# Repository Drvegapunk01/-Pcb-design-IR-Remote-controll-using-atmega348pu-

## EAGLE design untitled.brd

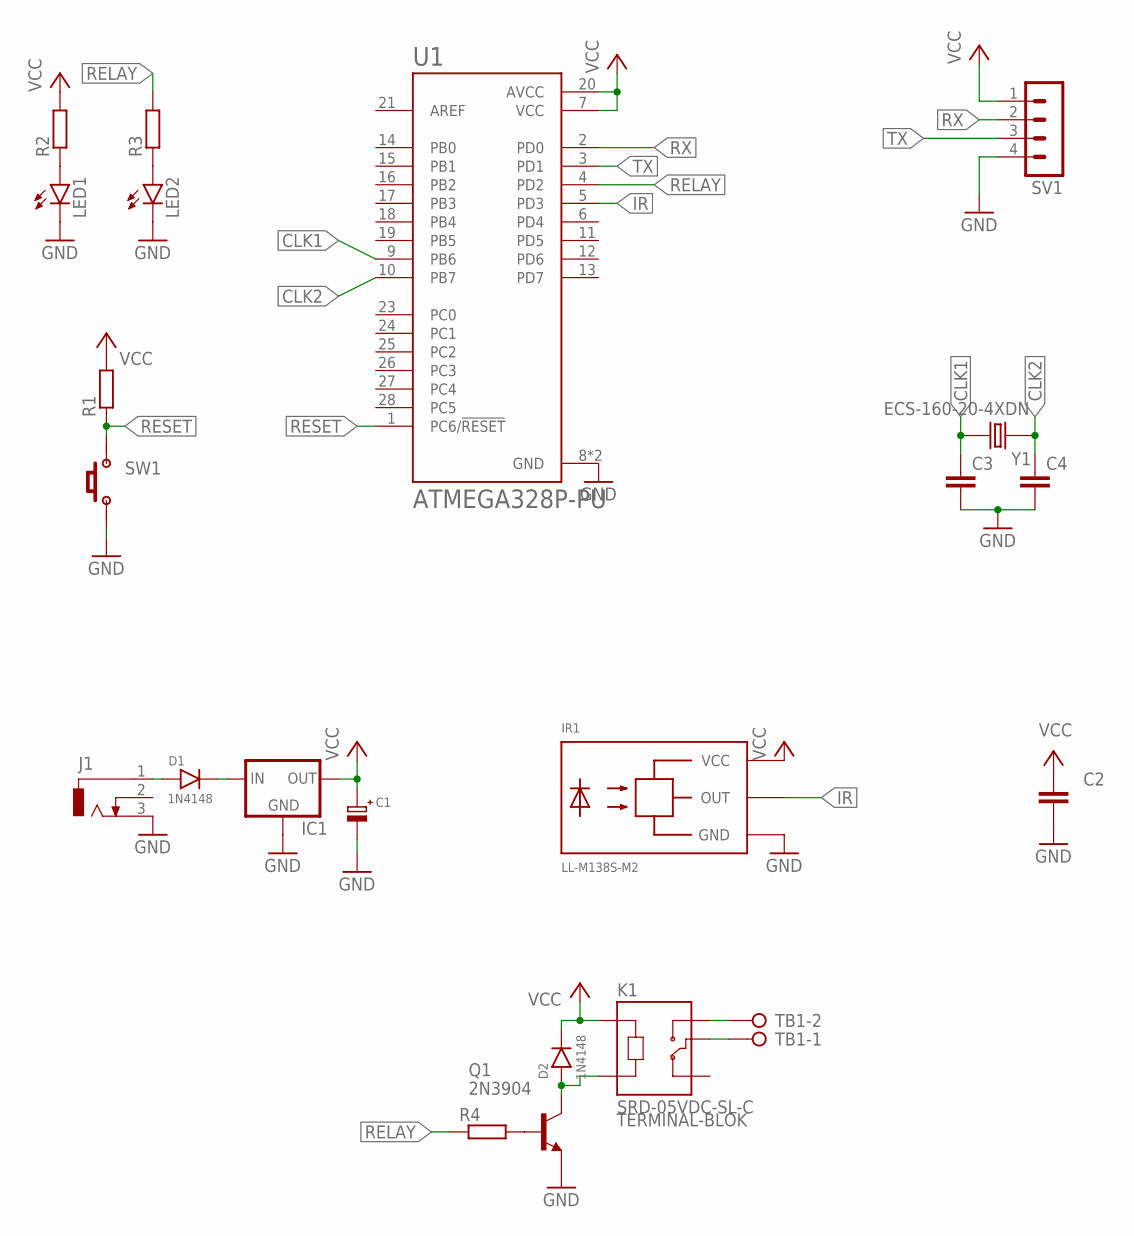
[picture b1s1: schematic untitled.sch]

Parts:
C1: CAP-ELCO; ELCO1
C2: CAP-NON; MKM
C3, C4: C-EU025-025X050; C025-025X050
D1, D2: 1N4148; DIODE
IC1: 78XXS
IR1: LL-M138S-M2
J1: DCJ0303
K1: SRD-05VDC-SL-C; RELAY_SRD-05VDC-SL-C
LED1, LED2: LED5MM
Q1: 2N3904; TO92-EBC
R1, R2, R3, R4: RES0207/10; 0207/10
SV1: MA04-1
SW1: PUSH_BUTTON4P; PUSH_BUTTON_4P
TB1: TERMINAL-BLOK; TB-2P
U1: ATMEGA328P-PU; DIP794W46P254L2967H457Q28B
Y1: ECS-160-20-4XDN; XTAL_ECS-160-20-4XDN

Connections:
CLK1: C3.1, U1.9 (PB6), Y1.2
CLK2: C4.1, U1.10 (PB7), Y1.1
GND: C1.2, C2.2, C3.2, C4.2, IC1.GND, IR1.GND, J1.3, LED1.K (C), LED2.K (C), Q1.E, SV1.4, SW1.1, SW1.2 (1), U1.8 (GND), U1.22 (GND)
IR: IR1.OUT, U1.5 (PD3)
unnamed: D1.1, J1.1
unnamed: D1.2, IC1.IN
unnamed: LED1.A, R2.1
unnamed: LED2.A, R3.1
unnamed: D2.1, K1.A2, Q1.C
unnamed: Q1.B, R4.2
unnamed: K1.NO, TB1.2
unnamed: K1.COM, TB1.1
RELAY: R3.2, R4.1, U1.4 (PD2)
RESET: R1.1, SW1.3 (2), SW1.4 (2), U1.1 (PC6/!RESET)
RX: SV1.2, U1.2 (PD0)
TX: SV1.3, U1.3 (PD1)
VCC: C1.1, C2.1, D2.2, IC1.OUT, IR1.VCC, K1.A1, R1.2, R2.2, SV1.1, U1.7 (VCC), U1.20 (AVCC)

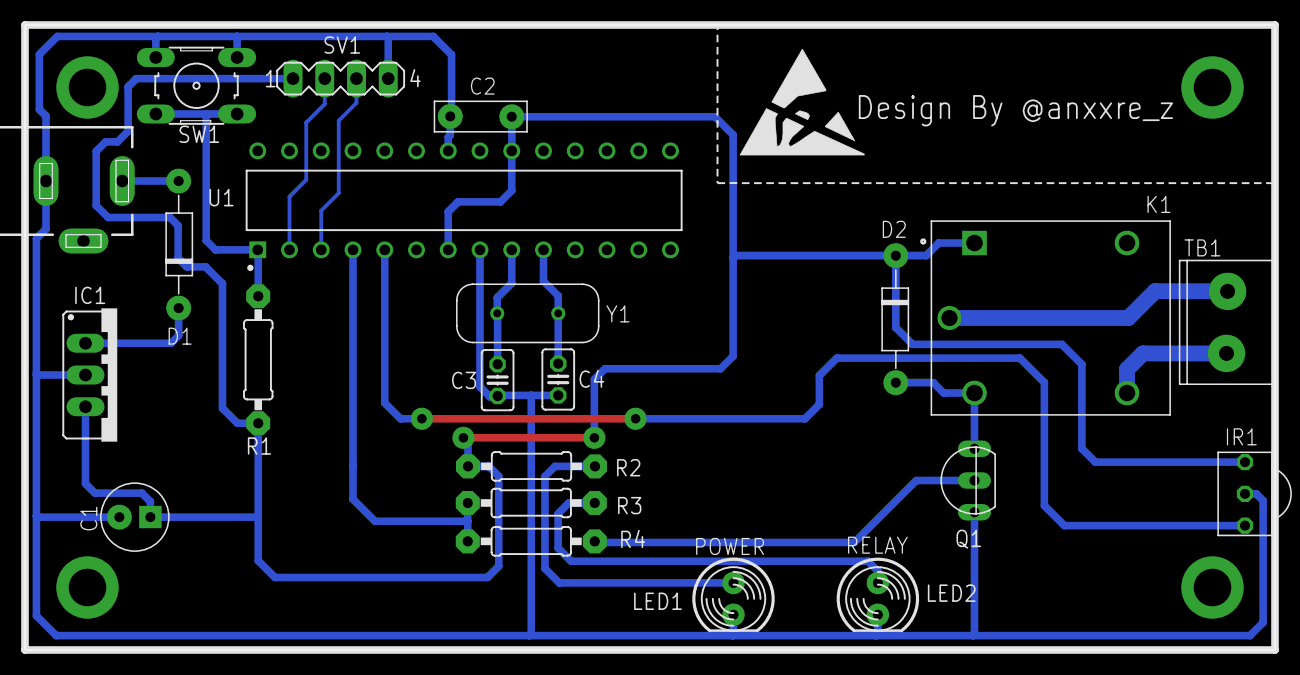
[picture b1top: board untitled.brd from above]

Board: 2 copper layers, 100.0 x 50.0 mm, 23 parts (0 on the bottom side), 17 nets.

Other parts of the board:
U$1: ESD_10.00
